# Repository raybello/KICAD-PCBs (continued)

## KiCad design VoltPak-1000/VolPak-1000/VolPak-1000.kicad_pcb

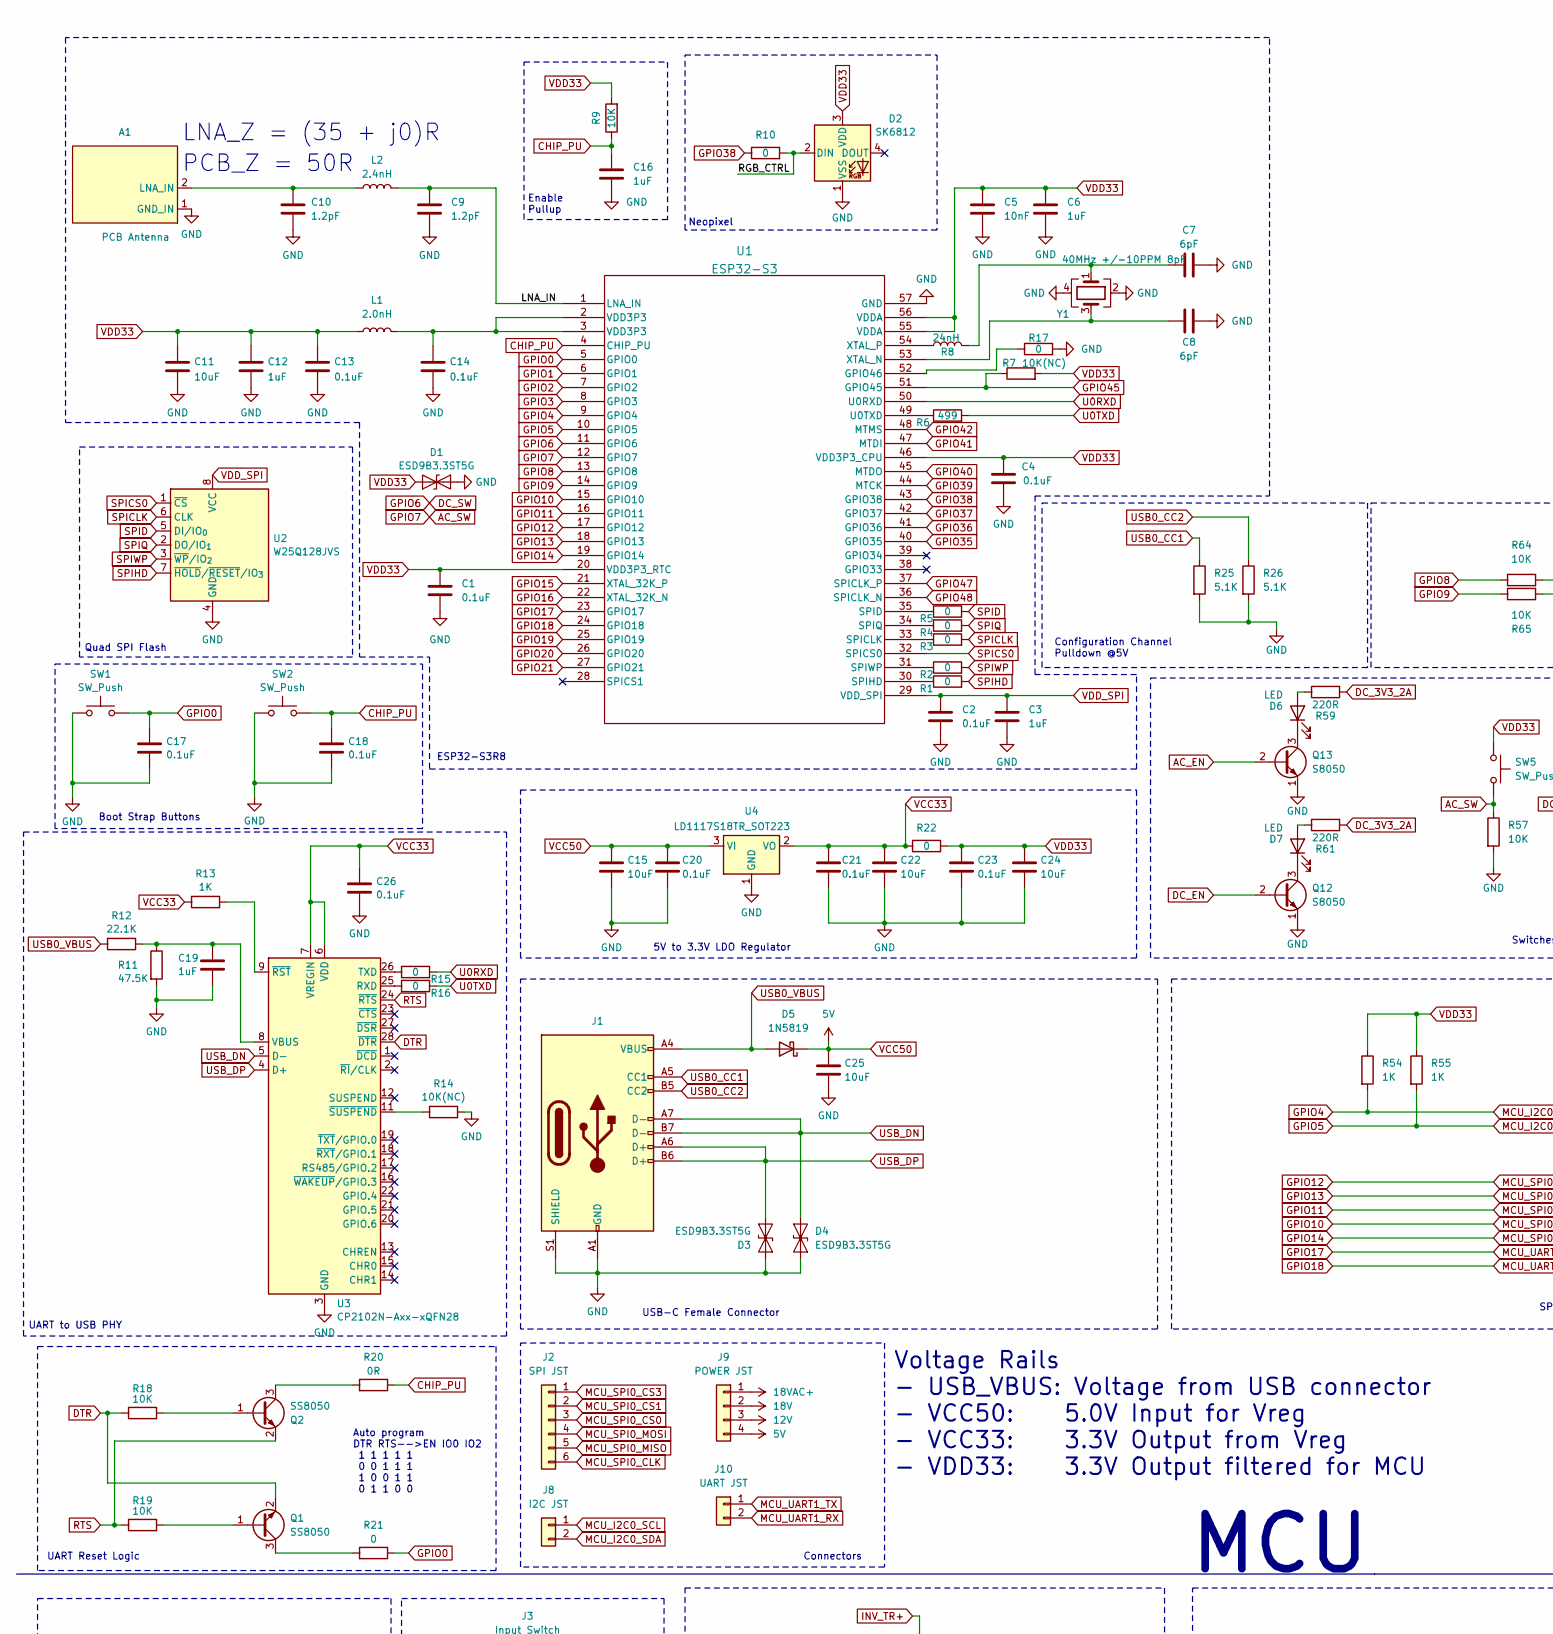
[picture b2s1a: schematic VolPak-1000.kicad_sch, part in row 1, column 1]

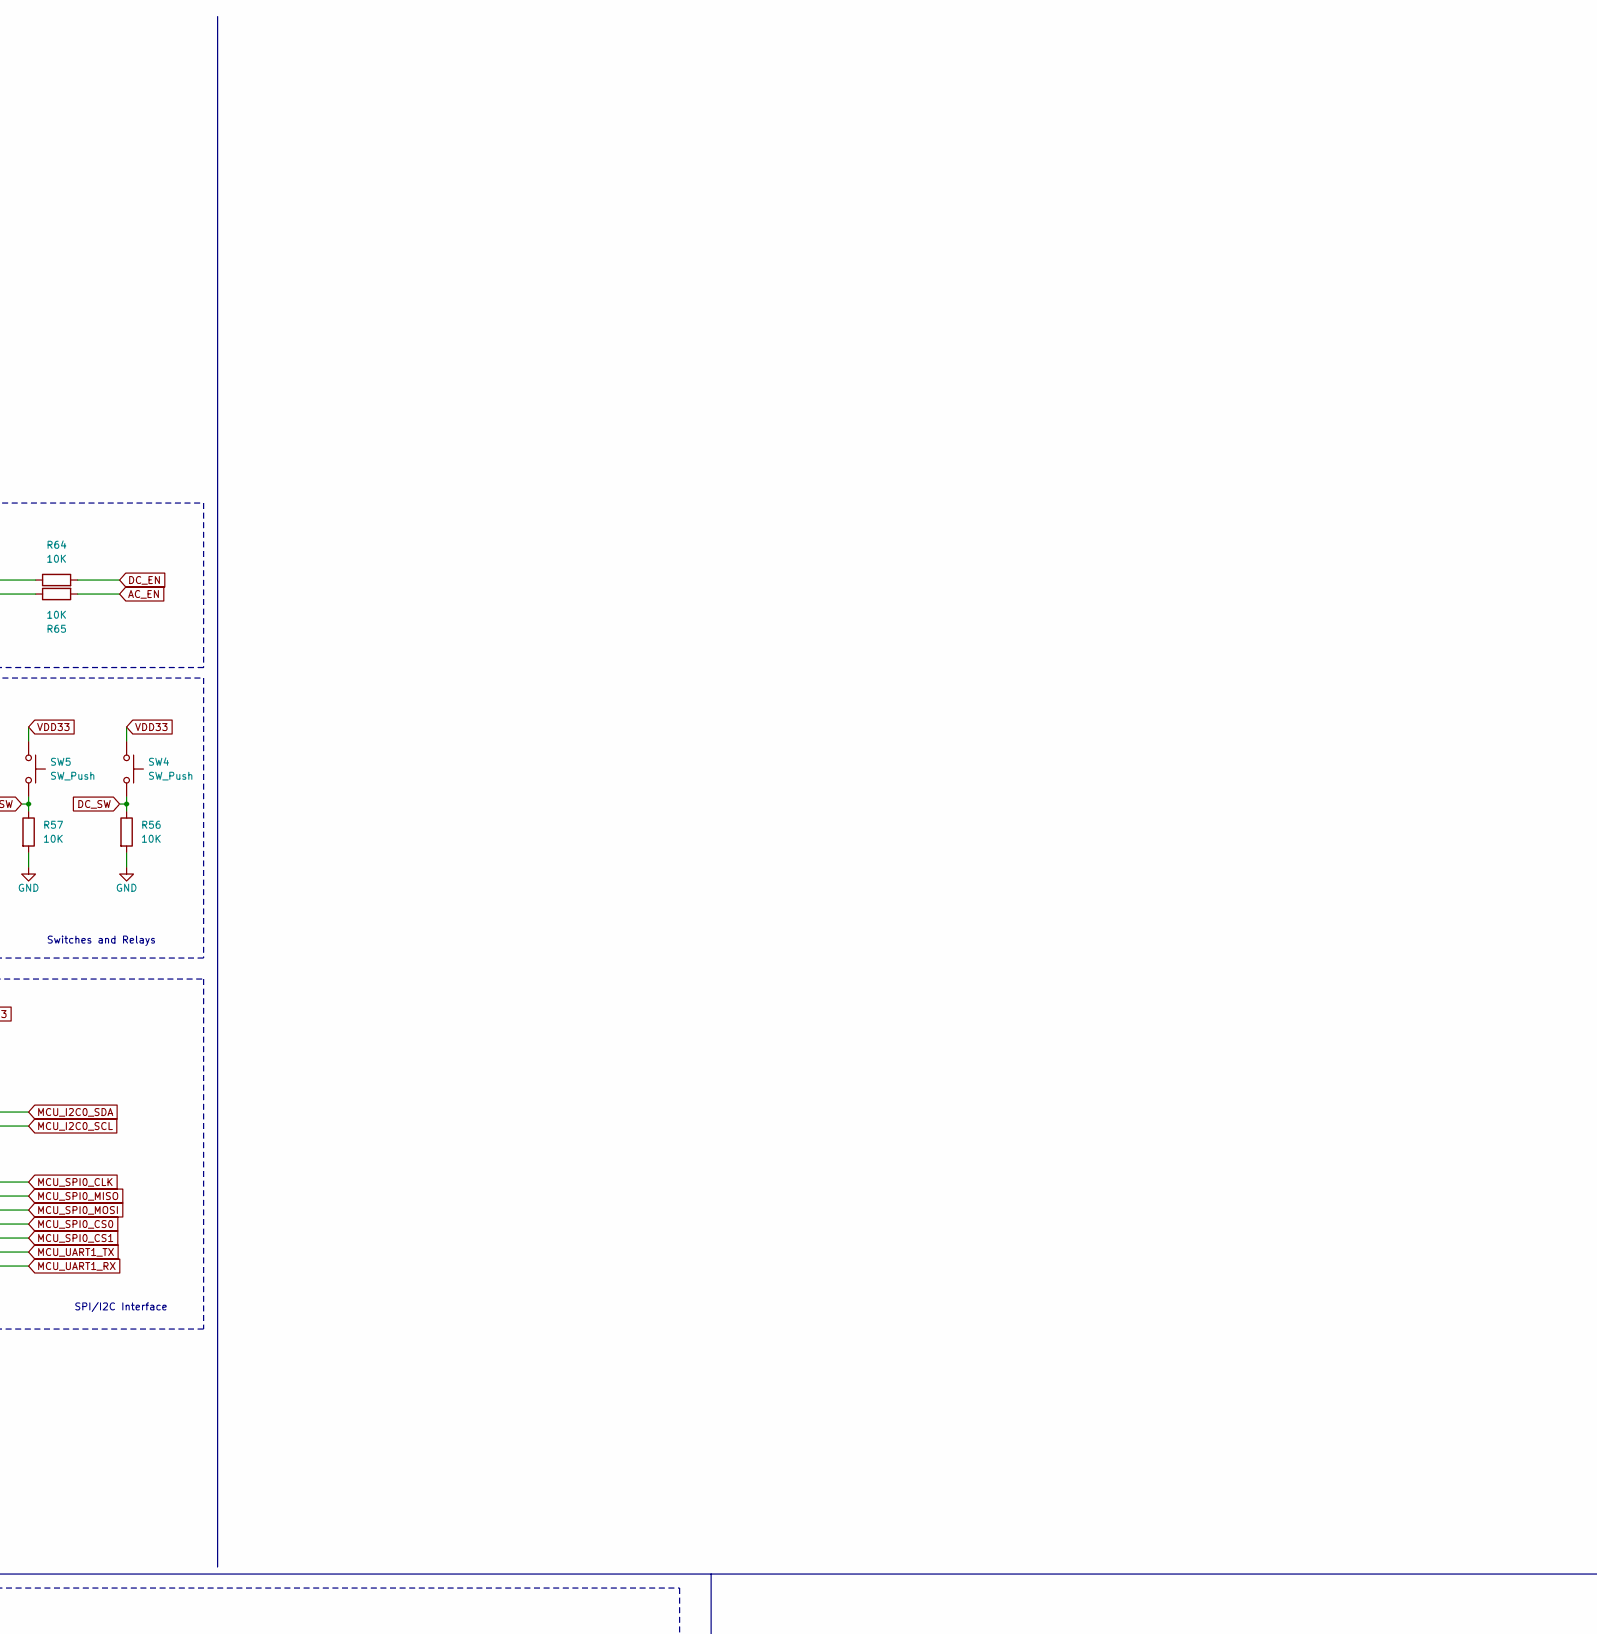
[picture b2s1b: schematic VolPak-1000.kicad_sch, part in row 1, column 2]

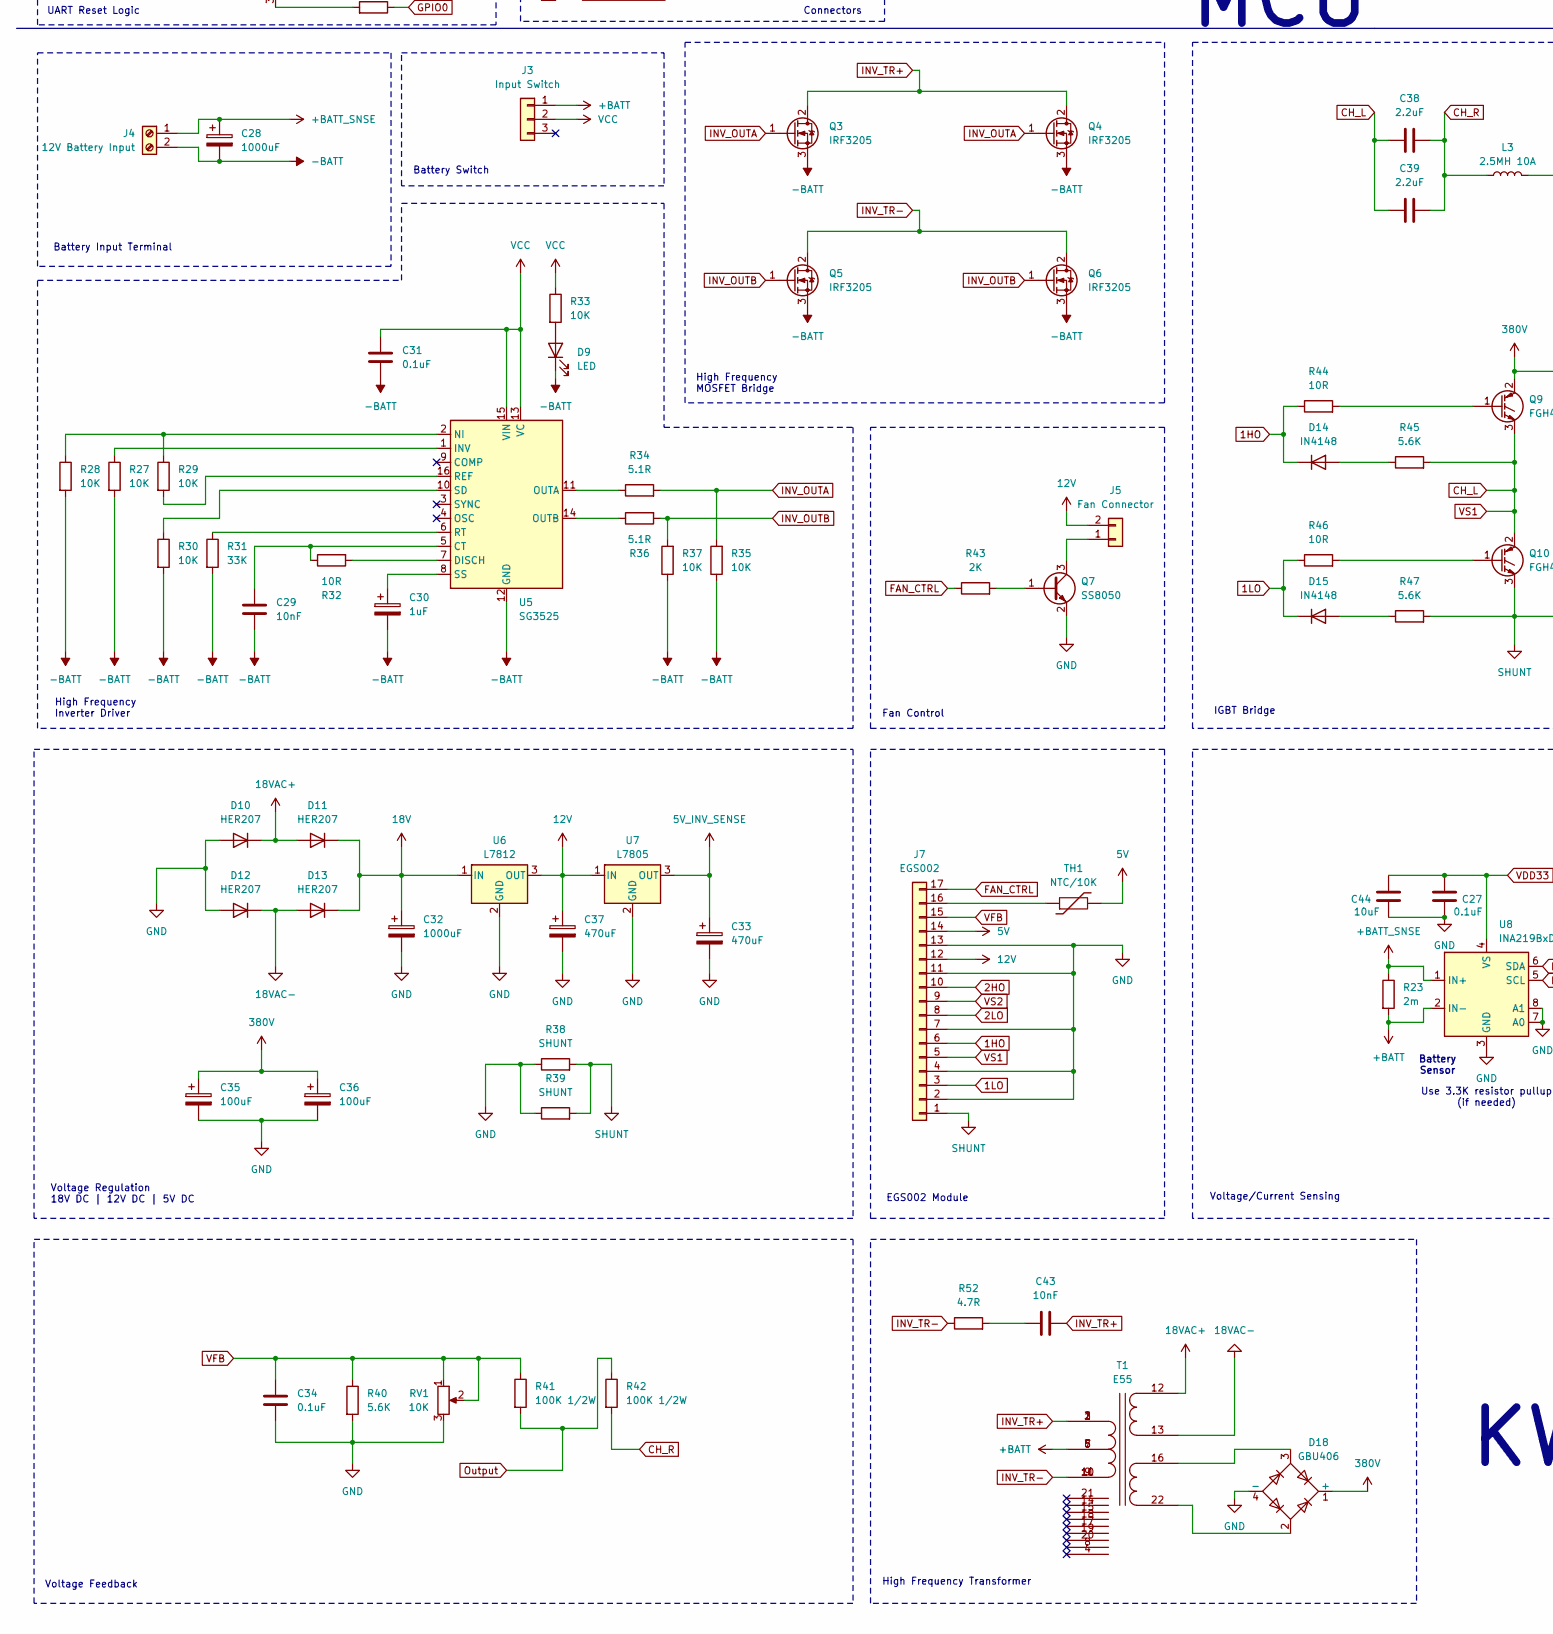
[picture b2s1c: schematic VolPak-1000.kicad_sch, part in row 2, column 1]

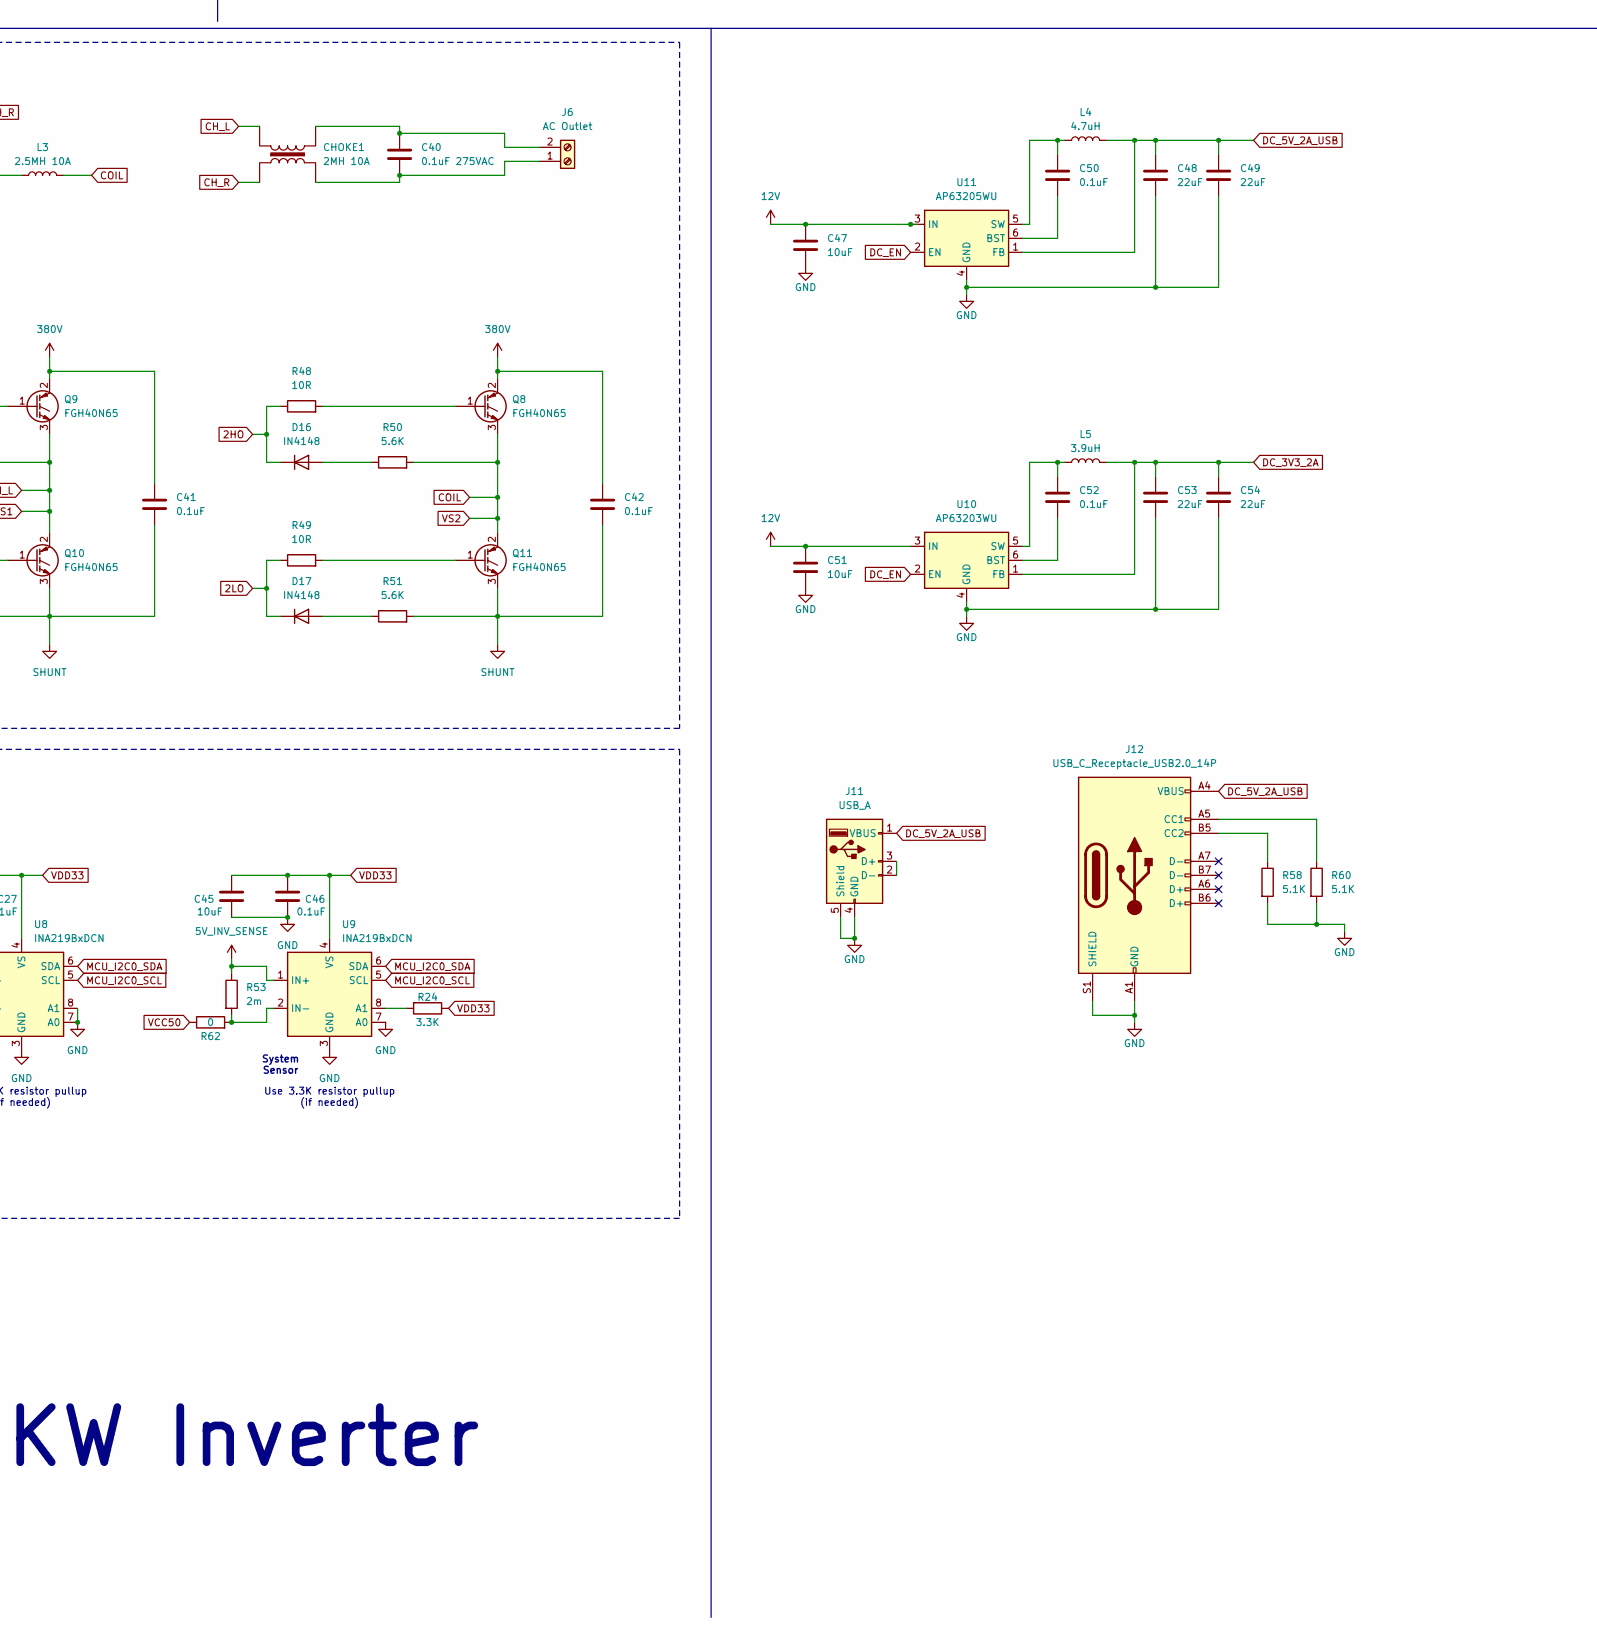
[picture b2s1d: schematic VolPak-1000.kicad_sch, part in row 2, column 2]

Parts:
A1: PCB Antenna; PCB_ANT
C1, C2, C4, C13, C14, C17, C18, C20, C21, C23, C26, C27, C31, C34, C46, C50, C52: 0.1uF; C_0402_1005Metric; LCSC C6119799
C3, C6, C12, C16, C19: 1uF; C_0402_1005Metric; LCSC C2887021
C5, C29: 10nF; C_0402_1005Metric; LCSC C688874
C7, C8: 6pF; C_0402_1005Metric; LCSC C437443
C9, C10: 1.2pF; C_0402_1005Metric; LCSC C880658
C11, C15, C22, C24, C25, C44, C45, C47, C51: 10uF; C_0402_1005Metric; LCSC C23692971
C28, C32: 1000uF; CP_Radial_D10.0mm_P5.00mm; LCSC C503217
C30: 1uF; CP_Radial_D5.0mm_P2.00mm; LCSC C2960204
C33, C37: 470uF; CP_Radial_D8.0mm_P3.80mm; LCSC C7499907
C35, C36: 100uF; CP_Radial_D18.0mm_P7.50mm; LCSC C2843909
C38, C39: 2.2uF; CP_Radial_D16.0mm_P7.50mm; LCSC C711636
C40: 0.1uF 275VAC; C_2220_5750Metric_Pad1.97x5.40mm_HandSolder; LCSC C5290327
C41, C42: 0.1uF; C_2220_5750Metric_Pad1.97x5.40mm_HandSolder; LCSC C5290327
C43: 10nF; C_0603_1608Metric; LCSC C100042
C48, C49, C53, C54: 22uF; C_0402_1005Metric; LCSC C415703
CHOKE1: 2MH 10A; Choke_Schaffner_RN216-04-15.5x23.0mm; LCSC C2831473
D1, D3, D4: ESD9B3.3ST5G; D_SOD-923; LCSC C5180230
D2: SK6812; LED_SK6812_PLCC4_5.0x5.0mm_P3.2mm; LCSC C5380881
D5: 1N5819; D_DO-41_SOD81_P10.16mm_Horizontal; LCSC C110032
D6, D7, D9: LED; LED_0603_1608Metric; LCSC C7501578
D10, D11, D12, D13: HER207; D_DO-15_P3.81mm_Vertical_KathodeUp; LCSC C31251
D14, D15, D16, D17: IN4148; D_DO-15_P3.81mm_Vertical_KathodeUp; LCSC C402212
D18: GBU406; Diode_Bridge_Vishay_GBU; LCSC C5632681
J1: USB_C_Receptacle_USB2.0_14P; USB_C_Receptacle_G-Switch_GT-USB-7010ASV; LCSC C2765186
J2: SPI JST; JST_EH_B6B-EH-A_1x06_P2.50mm_Vertical
J3: Input Switch; PinHeader_1x03_P2.54mm_Vertical
J4: 12V Battery Input; TerminalBlock_MaiXu_MX126-5.0-02P_1x02_P5.00mm; LCSC C8269
J5: Fan Connector; PinHeader_1x02_P2.54mm_Vertical
J6: AC Outlet; TerminalBlock_MaiXu_MX126-5.0-02P_1x02_P5.00mm; LCSC C8269
J7: EGS002; PinHeader_1x17_P2.54mm_Vertical
J8: I2C JST; JST_EH_B2B-EH-A_1x02_P2.50mm_Vertical
J9: POWER JST; JST_EH_B4B-EH-A_1x04_P2.50mm_Vertical
J10: UART JST; JST_EH_B2B-EH-A_1x02_P2.50mm_Vertical
J11: USB_A; USB_A_Molex_67643_Horizontal; LCSC C591765
J12: USB_C_Receptacle_USB2.0_14P; USB_C_C783299; LCSC C783299
L1: 2.0nH; L_0402_1005Metric; LCSC C76769
L2: 2.4nH; L_0402_1005Metric; LCSC C913678
L3: 2.5MH 10A; L_Toroid_Vertical_L48.8mm_W25.4mm_P20.80mm_Vishay_TJ8
L4: 4.7uH; L_0402_1005Metric; LCSC C18221128
L5: 3.9uH; L_0603_1608Metric; LCSC C22447690
Q1, Q2, Q7: SS8050; SOT-23; LCSC C2834467
Q3, Q4, Q5, Q6: IRF3205; TO-220-3_Vertical; LCSC C19189952
Q8, Q9, Q10, Q11: FGH40N65; TO-247-3_Vertical; LCSC C472600
Q12, Q13: S8050; TO-92_Inline; LCSC C2931492
R1, R2, R3, R4, R5, R10, R15, R16, R17, R21, R22, R62: 0; R_0402_1005Metric; LCSC C106231
R6: 499; R_0402_1005Metric; LCSC C137970
R7, R14: 10K(NC); R_0402_1005Metric; LCSC C60490
R8: 24nH; L_0402_1005Metric; LCSC C404641
R9, R18, R19, R56, R57, R64, R65: 10K; R_0402_1005Metric; LCSC C60490
R11: 47.5K; R_0402_1005Metric; LCSC C25896
R12: 22.1K; R_0402_1005Metric; LCSC C163478
R13, R54, R55: 1K; R_0402_1005Metric; LCSC C11702
R20: 0R; R_0402_1005Metric; LCSC C106231
R23, R53: 2m; R_0603_1608Metric
R24: 3.3K; R_0402_1005Metric; LCSC C137992
R25, R26, R58, R60: 5.1K; R_0402_1005Metric; LCSC C25905
R27, R28, R29, R30, R33, R35, R37: 10K; R_0603_1608Metric; LCSC C161787
R31: 33K; R_0603_1608Metric; LCSC C2907028
R32, R44, R46, R48, R49: 10R; R_0603_1608Metric; LCSC C109318
R34, R36: 5.1R; R_0603_1608Metric; LCSC C2907045
R38, R39: SHUNT; R_2512_6332Metric; LCSC C469426
R40, R45, R47, R50, R51: 5.6K; R_0603_1608Metric; LCSC C2907046
R41, R42: 100K 1/2W; R_0603_1608Metric; LCSC C491207
R43: 2K; R_0402_1005Metric; LCSC C4109
R52: 4.7R; R_0603_1608Metric; LCSC C137705
R59, R61: 220R; R_0402_1005Metric; LCSC C2909336
RV1: 10K; Potentiometer_Bourns_3296W_Vertical; LCSC C118954
SW1, SW2, SW4, SW5: SW_Push; SW_SPST_PTS810; LCSC C221895
T1: E55; Transformer_CHK_EI54-12VA_Neutral
TH1: NTC/10K; LCSC C394024
U1: ESP32-S3; QFN56_7X7_EXP
U2: W25Q128JVS; SOIC-8_5.3x5.3mm_P1.27mm; LCSC C113767
U3: CP2102N-Axx-xQFN28; QFN-28-1EP_5x5mm_P0.5mm_EP3.35x3.35mm; LCSC C964632
U4: LD1117S18TR_SOT223; SOT-223-3_TabPin2; LCSC C19627011
U5: SG3525; SOP-16_3.9x9.9mm_P1.27mm; LCSC C7598682
U6: L7812; TO-220-3_Vertical; LCSC C2914
U7: L7805; TO-220-3_Vertical; LCSC C3795
U8, U9: INA219BxDCN; SOT-23-8; LCSC C962069
U10: AP63203WU; TSOT-23-6; LCSC C780769
U11: AP63205WU; TSOT-23-6; LCSC C2071056
Y1: 40MHz +/-10PPM 8pF; Crystal_SMD_3225-4Pin_3.2x2.5mm; LCSC C7294596

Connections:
1HO: D14.1 (K), J7.6, R44.1
1LO: D15.1 (K), J7.3, R46.1
2HO: D16.1 (K), J7.10, R48.1
2LO: D17.1 (K), J7.8, R49.1
5V_INV_SENSE: C33.1, R53.1, U7.3 (OUT), U9.1 (IN+)
12V: C37.1, C47.1, C51.1, J5.2, J7.12, J9.3, U6.3 (OUT), U7.1 (IN), U10.3 (IN), U11.3 (IN)
18V: C32.1, D11.1 (K), D13.1 (K), J9.2, U6.1 (IN)
18VAC+: D10.1 (K), D11.2 (A), J9.1, T1.12 (OUT-)
18VAC-: D12.1 (K), D13.2 (A), T1.13 (NC13)
380V: C35.1, C36.1, C41.1, C42.1, D18.1 (+), Q8.2 (C), Q9.2 (C)
+BATT: J3.1, R23.2, T1.5 (VCC), T1.6 (VCC), T1.7 (VCC), U8.2 (IN-)
+BATT_SNSE: C28.1, J4.1, R23.1, U8.1 (IN+)
-BATT: C28.2, C29.2, C30.2, C31.2, D9.1 (K), J4.2, Q3.3 (S), Q4.3 (S), Q5.3 (S), Q6.3 (S), R27.2, R28.2, R30.2, R31.2, R35.1, R37.1, U5.12 (GND)
/LNA_IN: C9.1, L2.2, U1.1 (LNA_IN)
/RGB_CTRL: D2.2 (DIN), R10.2
AC_EN: Q13.2 (B), R65.2
AC_SW: R57.1, SW5.2, U1.12 (GPIO7)
CHIP_PU: C16.2, C18.2, R9.1, R20.1, SW2.2, U1.4 (CHIP_PU)
CH_L: C38.1, C39.1, CHOKE1.4, J7.5, Q9.3 (E), Q10.2 (C), R45.2
CH_R: C38.2, C39.2, CHOKE1.1, L3.1, R42.2
COIL: J7.9, L3.2, Q8.3 (E), Q11.2 (C), R50.2
DC_3V3_2A: C53.1, C54.1, L5.2, R59.2, R61.2, U10.1 (FB)
DC_5V_2A_USB: C48.1, C49.1, J11.1 (VBUS), J12.A4 (VBUS), J12.A9 (VBUS), J12.B4 (VBUS), J12.B9 (VBUS), L4.2, U11.1 (FB)
DC_EN: Q12.2 (B), R64.2, U10.2 (EN), U11.2 (EN)
DC_SW: R56.1, SW4.2, U1.11 (GPIO6)
DTR: Q1.2 (E), R18.1, U3.28 (~DTR)
FAN_CTRL: J7.17, R43.1
GND: A1.1 (GND_IN), C1.2, C2.2, C3.2, C4.2, C5.2, C6.2, C7.2, C8.1, C9.2, C10.2, C11.2, C12.2, C13.2, C14.2, C15.2, C16.1, C17.1, C18.1, C19.2, C20.2, C21.2, C22.2, C23.2, C24.2, C25.2, C26.1, C27.2, C32.2, C33.2, C34.2, C35.2, C36.2, C37.2, C44.2, C45.2, C46.2, C47.2, C48.2, C49.2, C51.2, C53.2, C54.2, D1.2 (A2), D2.1 (VSS), D3.2 (A2), D4.1 (A1), D10.2 (A), D12.2 (A), D18.4 (-), J1.A1 (GND), J1.A12 (GND), J1.B1 (GND), J1.B12 (GND), J1.S1 (SHIELD), J7.2, J7.4, J7.7, J7.11, J7.13, J11.4 (GND), J11.5 (Shield), J12.A1 (GND), J12.A12 (GND), J12.B1 (GND), J12.B12 (GND), J12.S1 (SHIELD), Q7.2 (E), Q12.1 (E), Q13.1 (E), R11.2, R14.2, R17.2, R25.2, R26.2, R38.1, R39.1, R40.2, R56.2, R57.2, R58.2, R60.2, RV1.3, SW1.1, SW2.1, U1.57 (GND), U2.4 (GND), U3.3 (GND), U3.29 (GND), U4.1 (GND), U6.2 (GND), U7.2 (GND), U8.3 (GND), U8.7 (A0), U8.8 (A1), U9.3 (GND), U9.7 (A0), U10.4 (GND), U11.4 (GND), Y1.2, Y1.4
GPIO0: C17.2, R21.1, SW1.2, U1.5 (GPIO0)
GPIO1: U1.6 (GPIO1)
GPIO2: U1.7 (GPIO2)
GPIO3: U1.8 (GPIO3)
GPIO4: J8.2, R54.2, U1.9 (GPIO4), U8.6 (SDA), U9.6 (SDA)
GPIO5: J8.1, R55.2, U1.10 (GPIO5), U8.5 (SCL), U9.5 (SCL)
GPIO8: R64.1, U1.13 (GPIO8)
GPIO9: R65.1, U1.14 (GPIO9)
GPIO10: J2.3, U1.15 (GPIO10)
GPIO11: J2.4, U1.16 (GPIO11)
GPIO12: J2.6, U1.17 (GPIO12)
GPIO13: J2.5, U1.18 (GPIO13)
GPIO14: J2.2, U1.19 (GPIO14)
GPIO15: U1.21 (XTAL_32K_P)
GPIO16: U1.22 (XTAL_32K_N)
GPIO17: J10.1, U1.23 (GPIO17)
GPIO18: J10.2, U1.24 (GPIO18)
GPIO19: U1.25 (GPIO19)
GPIO20: U1.26 (GPIO20)
GPIO21: U1.27 (GPIO21)
GPIO35: U1.40 (GPIO35)
GPIO36: U1.41 (GPIO36)
GPIO37: U1.42 (GPIO37)
GPIO38: R10.1, U1.43 (GPIO38)
GPIO39: U1.44 (MTCK)
GPIO40: U1.45 (MTDO)
GPIO41: U1.47 (MTDI)
GPIO42: U1.48 (MTMS)
GPIO45: R7.1, U1.51 (GPIO45)
GPIO47: U1.37 (SPICLK_P)
GPIO48: U1.36 (SPICLK_N)
INV_OUTA: Q3.1 (G), Q4.1 (G), R34.2, R35.2
INV_OUTB: Q5.1 (G), Q6.1 (G), R36.2, R37.2
INV_TR+: C43.1, Q3.2 (D), Q4.2 (D), T1.1 (IN-), T1.2 (IN-), T1.3 (IN-)
INV_TR-: Q5.2 (D), Q6.2 (D), R52.1, T1.9 (IN+), T1.10 (IN+), T1.11 (IN+)
MCU_SPI0_CS3: J2.1
unnamed: A1.2 (LNA_IN), C10.1, L2.1
unnamed: C7.1, R8.2, Y1.1
unnamed: C14.1, L1.2, U1.2 (VDD3P3), U1.3 (VDD3P3)
unnamed: C43.2, R52.2
unnamed: D6.2 (A), R59.1
unnamed: D6.1 (K), Q13.3 (C)
unnamed: D7.2 (A), R61.1
unnamed: D7.1 (K), Q12.3 (C)
unnamed: D9.2 (A), R33.2
unnamed: D14.2 (A), R45.1
unnamed: D15.2 (A), R47.1
unnamed: D16.2 (A), R50.1
unnamed: D17.2 (A), R51.1
unnamed: J5.1, Q7.3 (C)
unnamed: C40.2, CHOKE1.2, J6.1
unnamed: C40.1, CHOKE1.3, J6.2
unnamed: J7.16, TH1.1
unnamed: J11.2 (D-), J11.3 (D+)
unnamed: J12.A5 (CC1), R60.1
unnamed: J12.B5 (CC2), R58.1
unnamed: Q1.1 (B), R19.2
unnamed: Q1.3 (C), R21.2
unnamed: Q2.1 (B), R18.2
unnamed: Q2.3 (C), R20.2
unnamed: Q7.1 (B), R43.2
unnamed: Q8.1 (G), R48.2
unnamed: Q9.1 (G), R44.2
unnamed: Q10.1 (G), R46.2
unnamed: Q11.1 (G), R49.2
unnamed: D18.2, T1.22 (AUX+)
unnamed: D18.3, T1.16 (NC16)
unnamed: R17.1, U1.52 (GPIO46)
unnamed: R3.1, U1.33 (SPICLK)
unnamed: R5.1, U1.35 (SPID)
unnamed: R1.1, U1.30 (SPIHD)
unnamed: R4.1, U1.34 (SPIQ)
unnamed: R2.1, U1.31 (SPIWP)
unnamed: R6.1, U1.49 (U0TXD)
unnamed: C8.2, U1.53 (XTAL_N), Y1.3
unnamed: R8.1, U1.54 (XTAL_P)
unnamed: R16.2, U3.25 (RXD)
unnamed: R15.1, U3.26 (TXD)
unnamed: C19.1, R11.1, R12.1, U3.8 (VBUS)
unnamed: R13.2, U3.9 (~RST)
unnamed: R14.1, U3.11 (~SUSPEND)
unnamed: C29.1, R32.1, U5.5 (CT)
unnamed: R32.2, U5.7 (DISCH)
unnamed: R27.1, U5.1 (INV)
unnamed: R28.1, R29.1, U5.2 (NI)
unnamed: R34.1, U5.11 (OUTA)
unnamed: R36.1, U5.14 (OUTB)
unnamed: R29.2, U5.16 (REF)
unnamed: R31.1, U5.6 (RT)
unnamed: R30.1, U5.10 (SD)
unnamed: C30.1, U5.8 (SS)
unnamed: R24.2, U9.8 (A1)
unnamed: R53.2, R62.2, U9.2 (IN-)
unnamed: C52.2, U10.6 (BST)
unnamed: C52.1, L5.1, U10.5 (SW)
unnamed: C50.2, U11.6 (BST)
unnamed: C50.1, L4.1, U11.5 (SW)
Output: R41.2, R42.1
RTS: Q2.2 (E), R19.1, U3.24 (~RTS)
SHUNT: C41.2, C42.2, J7.1, Q10.3 (E), Q11.3 (E), R38.2, R39.2, R47.2, R51.2
SPICLK: R3.2, U2.6 (CLK)
SPICS0: U1.32 (SPICS0), U2.1 (~CS)
SPID: R5.2, U2.5 (DI/IO_{0})
SPIHD: R1.2, U2.7 (~HOLD/~RESET/IO_{3})
SPIQ: R4.2, U2.2 (DO/IO_{1})
SPIWP: R2.2, U2.3 (~WP/IO_{2})
U0RXD: R15.2, U1.50 (U0RXD)
U0TXD: R6.2, R16.1
USB0_CC1: J1.A5 (CC1), R25.1
USB0_CC2: J1.B5 (CC2), R26.1
USB0_VBUS: D5.2 (A), J1.A4 (VBUS), J1.A9 (VBUS), J1.B4 (VBUS), J1.B9 (VBUS), R12.2
USB_DN: D4.2 (A2), J1.A7 (D-), J1.B7 (D-), U3.5 (D-)
USB_DP: D3.1 (A1), J1.A6 (D+), J1.B6 (D+), U3.4 (D+)
VCC: C31.1, J3.2, R33.1, U5.13 (VC), U5.15 (VIN)
VCC33: C21.1, C22.1, C26.2, R13.1, R22.1, U3.6 (VDD), U3.7 (VREGIN), U4.2 (VO)
VCC50: C15.1, C20.1, C25.1, D5.1 (K), J7.14, J9.4, R62.1, TH1.2, U4.3 (VI)
VDD33: C1.1, C4.1, C5.1, C6.1, C11.1, C12.1, C13.1, C23.1, C24.1, C27.1, C44.1, C45.1, C46.1, D1.1 (A1), D2.3 (VDD), L1.1, R7.2, R9.2, R22.2, R24.1, R54.1, R55.1, SW4.1, SW5.1, U1.20 (VDD3P3_RTC), U1.46 (VDD3P3_CPU), U1.55 (VDDA), U1.56 (VDDA), U8.4 (VS), U9.4 (VS)
VDD_SPI: C2.1, C3.1, U1.29 (VDD_SPI), U2.8 (VCC)
VFB: C34.1, J7.15, R40.1, R41.1, RV1.1, RV1.2

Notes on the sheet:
Switches and Relays
UART to USB PHY
USB-C Female Connector
UART Reset Logic
Quad SPI Flash
KW Inverter
High Frequency Inverter Driver
IGBT Bridge
Connectors
Voltage Rails - USB_VBUS: Voltage from USB connector - VCC50: 5.0V Input for Vreg - VCC33: 3.3V Output from Vreg - VDD33: 3.3V Output filtered for MCU
Battery Switch
Use 3.3K resistor pullup (if needed)
ESP32-S3R8
Enable Pullup
Fan Control
Battery Sensor
Boot Strap Buttons
SPI/I2C Interface
LNA_Z = (35 + j0)R
5V to 3.3V LDO Regulator
Voltage/Current Sensing
High Frequency MOSFET Bridge
Auto program DTR RTS-->EN IO0 IO2 1 1 1 1 1 0 0 1 1 1 1 0 0 1 1 0 1 1 0 0
EGS002 Module
Neopixel
Voltage Feedback
High Frequency Transformer
Voltage Regulation 18V DC | 12V DC | 5V DC
Battery Input Terminal
MCU
System Sensor
PCB_Z = 50R
Configuration Channel Pulldown @5V

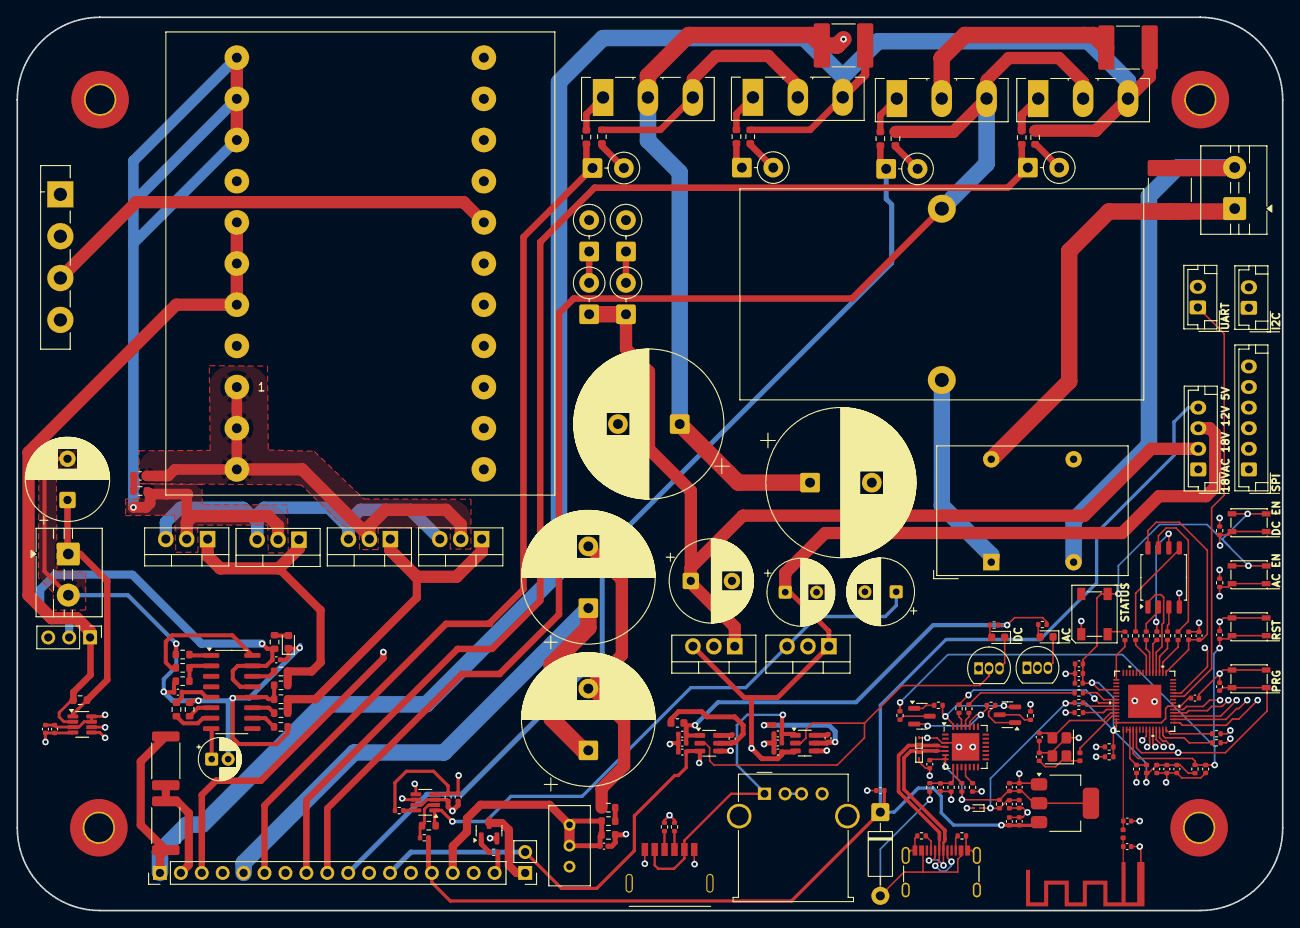
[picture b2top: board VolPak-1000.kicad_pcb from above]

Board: 4 copper layers, 153.7 x 108.5 mm, 185 parts (0 on the bottom side), 128 nets.

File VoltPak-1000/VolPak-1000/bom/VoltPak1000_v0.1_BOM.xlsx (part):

| VOLTPAK 1000 v0.1 Bill Of Materials
 | PRODUCT NAME | VoltPak 1000 v0.1 | CONTACT INFO
 | APPROVED BY | Ray B.
 | APPROVAL DATE | 03/09/2025
 | PART COUNT | 81
 | TOTAL COST | 67.234700000000032
 | ITEM NUMBER | ITEM NAME | DESCRIPTION | QUANTITY | ORDER QUANTITY | SOURCE / SUPPLIER | LINK TO SUPPORTING DOC | MFN | VALIDATED | STATUS | UNIT COST | BOARD COST | TOTAL PART COST |  | LEGEND
 | 1 | A1 | PCB Antenna | 1 | 1 |  |  |  | VALIDATED |  | 0 | 0 | 0 |  | VALIDATED
 | 2 | C1, C13, C14, C17, C18, C2, C20, C21, C23, C26, C27, C31, C34, C | 16V 100nF X7R ±10% 0402 Multilayer Ceramic Capacitors MLCC - SMD/SMT ROHS | 17 | 100 | C6119799 | https://www.lcsc.com/product-detail/C6119799.html | CGA0402X7R104K160GT | VALIDATED | IN CART | 8.9999999999999998E-4 | 1.5299999999999999E-2 | 0.09 |  | IN CART
 | 3 | C10, C9 | 50V 1.2pF C0G 0402 Multilayer Ceramic Capacitors MLCC - SMD/SMT ROHS | 2 | 100 | C880658 | https://www.lcsc.com/product-detail/C880658.html | TCC0402COG1R2C500AT | VALIDATED |  | 8.9999999999999998E-4 | 1.8E-3 | 0.09 |  | ORDERED
 | 4 | C11, C15, C22, C24, C25, C44, C45, C47, C51 | 6.3V 10uF X5R ±20% 0402 Multilayer Ceramic Capacitors MLCC - SMD/SMT ROHS | 9 | 100 | C23692971 | https://www.lcsc.com/product-detail/C23692971.html | CGA0402X5R106M6R3GT | VALIDATED |  | 5.3E-3 | 4.7699999999999999E-2 | 0.53 |  | COMPLETE
 | 5 | C12, C16, C19, C3, C6 | 6.3V 1uF X5R ±20% 0402 Multilayer Ceramic Capacitors MLCC - SMD/SMT ROHS | 5 | 100 | C2887021 | https://www.lcsc.com/product-detail/C2887021.html | TCC0402X5R105M6R3AT | VALIDATED |  | 1.5E-3 | 7.4999999999999997E-3 | 0.15
 | 6 | C28, C32 | 1000uF 25V ±20% 450mA@120Hz Through Hole,D10xL16mm Aluminum Electrolytic Capaci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 | 2 | 10 | C503217 | https://www.lcsc.com/product-detail/C503217.html | 01EC4294SHC1000UF25V | VALIDATED |  | 5.2999999999999999E-2 | 0.106 | 0.53
 | 7 | C29, C5 | 50V 10nF X7R ±10% 0402 Multilayer Ceramic Capacitors MLCC - SMD/SMT ROHS | 2 | 100 | C688874 | https://www.lcsc.com/product-detail/C688874.html | TCC0402X7R103K500AT | VALIDATED |  | 8.9999999999999998E-4 | 1.8E-3 | 0.09
 | 8 | C30 | 1uF 50V ±20% Through Hole,D5xL11mm Aluminum Electrolytic Capacitors - Leaded RO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 | 1 | 50 | C2960204 | https://www.lcsc.com/product-detail/C2960204.html | 50V1uF CD110 | VALIDATED |  | 7.7999999999999996E-3 | 7.7999999999999996E-3 | 0.38999999999999996
 | 9 | C33, C37 | 470uF 16V Through Hole,D8xL9mm Aluminum Electrolytic Capacitors - Leaded ROHS | 2 | 20 | C7499907 | https://www.lcsc.com/product-detail/C7499907.html | CD288477M1C0809VFL | VALIDATED |  | 2.4799999999999999E-2 | 4.9599999999999998E-2 | 0.496
 | 10 | C35, C36 | 100uF 450V ±20% 880mA@120kHz Through Hole,D18xL36mm Aluminum Electrolytic Capac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 | 2 | 2 | C2843909 | https://www.lcsc.com/product-detail/C2843909.html | KF101M45018*36A | VALIDATED |  | 0.7621 | 1.5242 | 1.5242
 | 11 | C38, C39 | 2.2uF 450V ±20% Through Hole,D6.3xL12mm Aluminum Electrolytic Capacitors - Lead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 | 2 | 20 | C711636 | https://www.lcsc.com/product-detail/C711636.html | ECG2WM2R2E12OTBO | VALIDATED |  | 3.73E-2 | 7.46E-2 | 0.746
 | 12 | C40 | 2kV 100nF X7R ±10% 2220 Multilayer Ceramic Capacitors MLCC - SMD/SMT ROHS | 1 | 1 | C5290327 | https://www.lcsc.com/product-detail/C5290327.html | FV55X104K202EGG | VALIDATED |  | 0.52210000000000001 | 0.52210000000000001 | 0.52210000000000001
 | 13 | C41, C42 | 2kV 100nF X7R ±10% 2220 Multilayer Ceramic Capacitors MLCC - SMD/SMT ROHS | 2 | 2 | C5290327 | https://www.lcsc.com/product-detail/C5290327.html | FV55X104K202EGG | VALIDATED |  | 0.52210000000000001 | 1.0442 | 1.0442
 | 14 | C43 | 50V 10nF X7R ±10% 0603 Multilayer Ceramic Capacitors MLCC - SMD/SMT ROHS | 1 | 100 | C100042 | https://www.lcsc.com/product-detail/C100042.html | CC0603KRX7R9BB103 | VALIDATED |  | 2.2000000000000001E-3 | 2.2000000000000001E-3 | 0.22
 | 15 | C48, C49, C53, C54 | 6.3V 22uF X5R ±20% 0402 Multilayer Ceramic Capacitors MLCC - SMD/SMT ROHS | 4 | 20 | C415703 | https://www.lcsc.com/product-detail/C415703.html | GRM155R60J226ME11D | VALIDATED |  | 3.3099999999999997E-2 | 0.13239999999999999 | 0.66199999999999992
 | 16 | C7, C8 | 50V 6pF C0G 0402 Multilayer Ceramic Capacitors MLCC - SMD/SMT ROHS | 2 | 50 | C437443 | https://www.lcsc.com/product-detail/C437443.html | GCM1555C1H6R0BA16D | VALIDATED |  | 1.2699999999999999E-2 | 2.5399999999999999E-2 | 0.63500000000000001
 | 17 | CHOKE1 | 2mH@1kHz 12mΩ 2 Through Hole,22x12mm Common Mode Filters ROHS | 1 | 1 | C2831473 | https://www.lcsc.com/product-detail/C2831473.html | PDMCAT18107-202ML | VALIDATED |  | 0.92049999999999998 | 0.92049999999999998 | 0.92049999999999998
 | 18 | D1, D3, D4 | 12A 100W 8V 3.7V Bidirectional 3.3V SOD-923 ESD and Surge Protection (TVS/ESD) 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 | 3 | 5 | C5180230 | https://www.lcsc.com/product-detail/C5180230.html | ESD9B3.3ST5G-ES | VALIDATED |  | 1.4800000000000001E-2 | 4.4400000000000002E-2 | 7.400000000000001E-2
 | 19 | D10, D11, D12, D13 | 1.7V@2A 70ns 2A 800V DO-15 Fast Recovery / High Efficiency Diodes ROHS | 4 | 20 | C31251 | https://www.lcsc.com/product-detail/C31251.html | HER207 | VALIDATED |  | 2.8799999999999999E-2 | 0.1152 | 0.57599999999999996
 | 20 | D14, D15, D16, D17 | 75V 1V@10mA 4ns 150mA DO-35 Switching Diodes ROHS | 4 | 50 | C402212 | https://www.lcsc.com/product-detail/C402212.html | 1N4148 | VALIDATED |  | 8.9999999999999993E-3 | 3.5999999999999997E-2 | 0.44999999999999996
 | 21 | D18 | 320A 1V@2A 4A 600V GBU Bridge Rectifiers ROHS | 1 | 5 | C5632681 | https://www.lcsc.com/product-detail/C5632681.html | GBU406_HF | VALIDATED |  | 0.27360000000000001 | 0.27360000000000001 | 1.3680000000000001
 | 22 | D2 | SMD5050-4P RGB LEDs(Built-in IC) ROHS | 1 | 5 | C5380881 | https://www.lcsc.com/product-detail/C5380881.html | SK6812-B | VALIDATED |  | 8.1900000000000001E-2 | 8.1900000000000001E-2 | 0.40949999999999998
 | 23 | D5 | 40V 550mV@1A 1A DO-41 Schottky Diodes ROHS | 1 | 10 | C110032 | https://www.lcsc.com/product-detail/C110032.html | 1N5819 | VALIDATED |  | 7.3099999999999998E-2 | 7.3099999999999998E-2 | 0.73099999999999998
 | 24 | D6, D7, D9 | 20mA 360mcd -30℃~+85℃ White 130° 68mW 2.4V~3.4V 0603 LED Indication - Discrete 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 | 3 | 50 | C7501578 | https://www.lcsc.com/product-detail/C7501578.html | NCD0603W6 | VALIDATED |  | 9.7000000000000003E-3 | 2.9100000000000001E-2 | 0.48499999999999999
 | 25 | J1 | 3A 1 Surface Mount, Right Angle 16P Female -25℃~+85℃ Type-C SMD USB Connectors 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 | 1 | 10 | C2765186 | https://www.lcsc.com/product-detail/C2765186.html | TYPE-C 16PIN 2MD(073) | VALIDATED |  | 5.79E-2 | 5.79E-2 | 0.57899999999999996
 | 26 | J10 | 1x2P 2P EH Tin 2 -25℃~+85℃ 3A 1 2.5mm Brass Through Hole Through Hole,P=2.5mm W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 | 1 | 20 | C160262 | https://www.lcsc.com/product-detail/C160262.html | B2B-EH-A(LF)(SN) | VALIDATED |  | 3.5700000000000003E-2 | 3.5700000000000003E-2 | 0.71400000000000008
 | 27 | J11 | USB 2.0 1 Right Angle 4P Female -55℃~+85℃ Type-A Through Hole USB Connectors RO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 | 1 | 1 | C591765 | https://www.lcsc.com/product-detail/C591765.html | 292303-6 | VALIDATED |  | 0.999 | 0.999 | 0.999
 | 28 | J12 | USB 3.1 3A 1 Surface Mount, Right Angle 6P Female -30℃~+85℃ Type-C SMD USB Conn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 | 1 | 1 | C783299 | https://www.lcsc.com/product-detail/C783299.html | USBC-0032IPX8-00 | VALIDATED |  | 0.75529999999999997 | 0.75529999999999997 | 0.75529999999999997
 | 29 | J2 | 1x6P 6P EH Tin 6 -25℃~+85℃ 3A 1 2.5mm Brass Through Hole Through Hole,P=2.5mm W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 | 1 | 5 | C160255 | https://www.lcsc.com/product-detail/C160255.html | B6B-EH-A(LF)(SN) |  |  | 3.9600000000000003E-2 | 3.9600000000000003E-2 | 0.19800000000000001
 | 30 | J3 | - | 1 |  | - |  | - |  |  | 0 | 0 | 0
 | 31 | J4 | 1x2P 20A -40℃~+105℃ 250V Green 12~22 Through Hole 5mm 2.5 1 2 Through Hole,P=5m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 | 1 | 5 | C8269 | https://www.lcsc.com/product-detail/C8269.html | WJ128V-5.0-2P |  |  | 0.12189999999999999 | 0.12189999999999999 | 0.60949999999999993
 | 32 | J5 | - | 1 |  | - |  | - |  |  | 0 | 0 | 0
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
